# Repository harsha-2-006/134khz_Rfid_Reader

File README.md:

# 134.2 kHz RFID Reader (EM4095 + ESP32)

A low-frequency RFID reader designed and built to explore the fundamentals of LF RFID communication systems at 134.2 kHz.

This project uses the EM4095 RFID analog front-end with an ESP32 for signal processing and data handling. A custom PCB with an integrated coil antenna was designed specifically for this implementation.

---

## Overview

The system operates at 134.2 kHz and detects compatible LF RFID tags through magnetic field coupling. The EM4095 handles signal amplification and demodulation, while the ESP32 processes the received data.

The project was developed as a practical hardware learning experience covering:
- RFID communication principles
- Analog front-end interfacing
- Coil antenna design
- PCB design and testing
- Embedded firmware development

---

## Features

- 134.2 kHz low-frequency RFID operation
- Custom-designed PCB
- Integrated PCB coil antenna
- EM4095 RFID analog front-end
- ESP32-based data processing
- Compact hardware design

---

## System Architecture

1. The PCB coil antenna generates a magnetic field at 134.2 kHz.
2. When an RFID tag enters the field, the tag modulates the carrier signal.
3. The EM4095 detects and demodulates the received signal.
4. The ESP32 reads and processes the decoded data.

---

## Project Images

### PCB Layout

### 3D View

### Schematic

To refresh the images after a design change, run from `hardware/` (needs KiCad ≥ 9, `rsvg-convert` and ImageMagick):

```sh
kicad-cli pcb export svg --mode-single --fit-page-to-board --exclude-drawing-sheet --layers B.Silkscreen,B.Cu,F.Cu,F.Silkscreen,F.Fab,Edge.Cuts -o "../images/pcb.svg" "Rfid em.kicad_pcb"
rsvg-convert -w 1600 -b '#001023' "../images/pcb.svg" -o "../images/Screenshot 2026-03-31 210803.png"
kicad-cli pcb render --side top --quality high --background opaque -w 1600 --height 1000 --zoom 1.2 -o "../images/Screenshot 2026-03-31 210818.png" "Rfid em.kicad_pcb"
kicad-cli sch export svg --exclude-drawing-sheet -o ../images "Rfid em.kicad_sch"
rsvg-convert -w 4000 -b white "../images/Rfid em.svg" | magick - -trim +repage -fuzz 2% -trim +repage -bordercolor "#f5f4ef" -border 40 "../images/Screenshot 2026-03-31 210833.png"
rm "../images/pcb.svg" "../images/Rfid em.svg"
```

---

## Hardware Components

- EM4095 RFID IC
- ESP32
- Custom PCB coil antenna

---

## Repository Structure

```text
hardware/   -> PCB layout and schematic files
software/   -> ESP32 firmware
images/     -> Project images

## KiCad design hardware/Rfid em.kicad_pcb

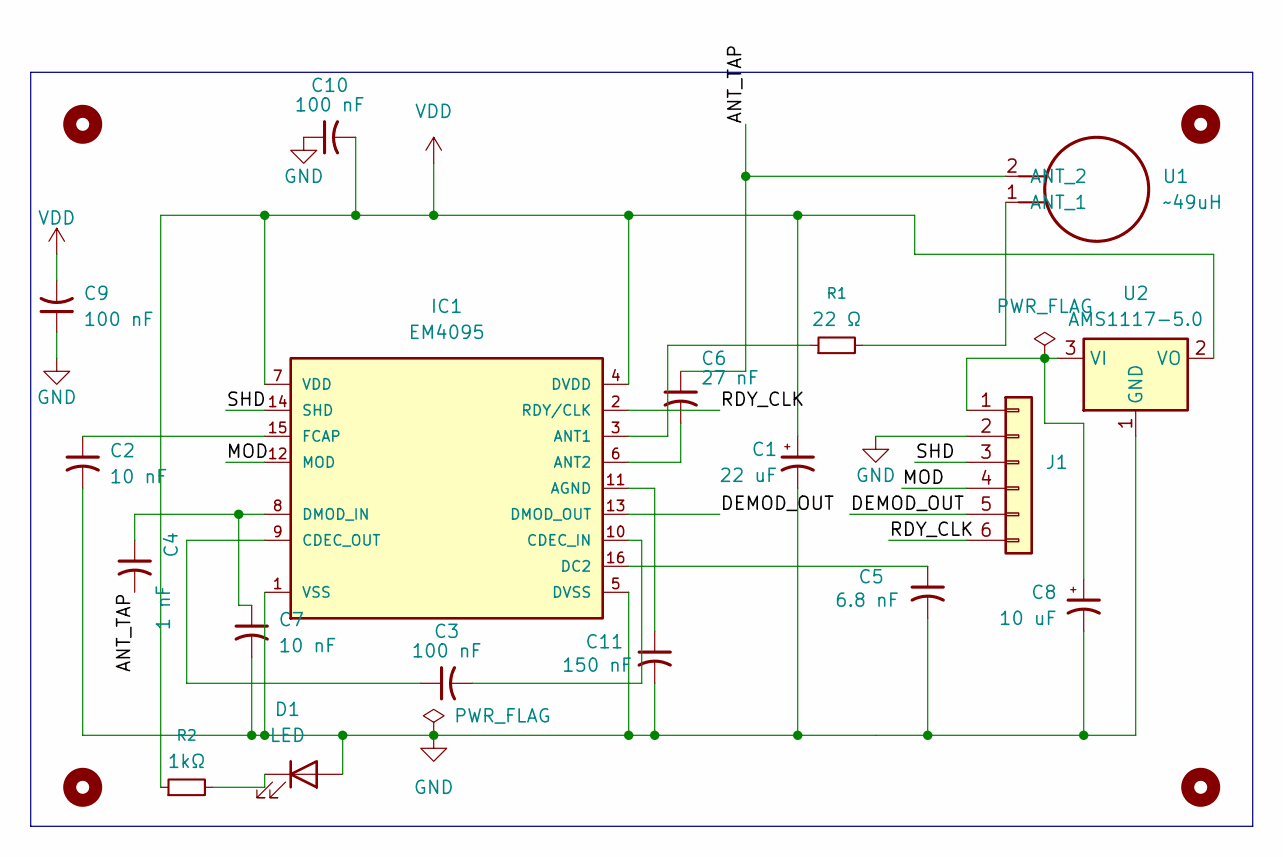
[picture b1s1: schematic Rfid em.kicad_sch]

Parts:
C1: 22 uF; CP_EIA-3528-21_Kemet-B; MPN T491B226K016AT
C2: 10 nF; C_0805_2012Metric; MPN C0805C103K5RACTU
C3, C9: 100 nF; C_0805_2012Metric; MPN GRM21BR71H104KA01L
C4: 1 nF; C_0805_2012Metric; MPN GRM2195C1H102JA01D
C5: 6.8 nF; C_0805_2012Metric; MPN C0805C682K5RACTU
C6: 27 nF; C_0805_2012Metric; MPN GRM2165C1H273JA01D
C7: 10 nF; C_0805_2012Metric; MPN GRM2195C1H103JA01D
C8: 10 uF; CP_EIA-6032-28_Kemet-C; MPN T491C106K035AT
C10: 100 nF; C_0603_1608Metric; MPN C0603C104K5RACTU
C11: 150 nF; C_0805_2012Metric; MPN C0805C154K5RACTU
D1: LED; LED_1206_3216Metric; MPN 158301250
H1, H2, H3, H4: MountingHole; MountingHole_3.5mm
IC1: EM4095; SOIC-16_3.9x9.9mm_P1.27mm; MPN EM4095HMSO16B
J1: Conn_01x06; PinHeader_1x06_P2.54mm_Vertical; MPN 61300611121
R1: 22 Ω; R_2512_6332Metric; MPN RC2512FK-0722RL
R2: 1kΩ; R_1206_3216Metric; MPN CRCW12061K00FKEA
U1: ~49uH; RFID_COIL
U2: AMS1117-5.0; SOT-223-3_TabPin2; MPN AMS1117-5.0

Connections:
/ANT_TAP: C4.2, C6.1, U1.2 (ANT_2)
/DEMOD_OUT: IC1.13 (DMOD_OUT), J1.5
/MOD: IC1.12 (MOD), J1.4
/RDY_CLK: IC1.2 (RDY/CLK), J1.6
/SHD: IC1.14 (SHD), J1.3
GND: C1.2, C2.2, C5.2, C7.2, C8.2, C9.1, C10.1, C11.2, D1.2 (A), IC1.1 (VSS), IC1.5 (DVSS), J1.2, U2.1 (GND)
unnamed: D1.1 (K), R2.2
unnamed: C11.1, IC1.11 (AGND)
unnamed: IC1.3 (ANT1), R1.1
unnamed: C6.2, IC1.6 (ANT2)
unnamed: C3.2, IC1.10 (CDEC_IN)
unnamed: C3.1, IC1.9 (CDEC_OUT)
unnamed: C5.1, IC1.16 (DC2)
unnamed: C4.1, C7.1, IC1.8 (DMOD_IN)
unnamed: C2.1, IC1.15 (FCAP)
unnamed: C8.1, J1.1, U2.3 (VI)
unnamed: R1.2, U1.1 (ANT_1)
VDD: C1.1, C9.2, C10.2, IC1.4 (DVDD), IC1.7 (VDD), R2.1, U2.2 (VO)

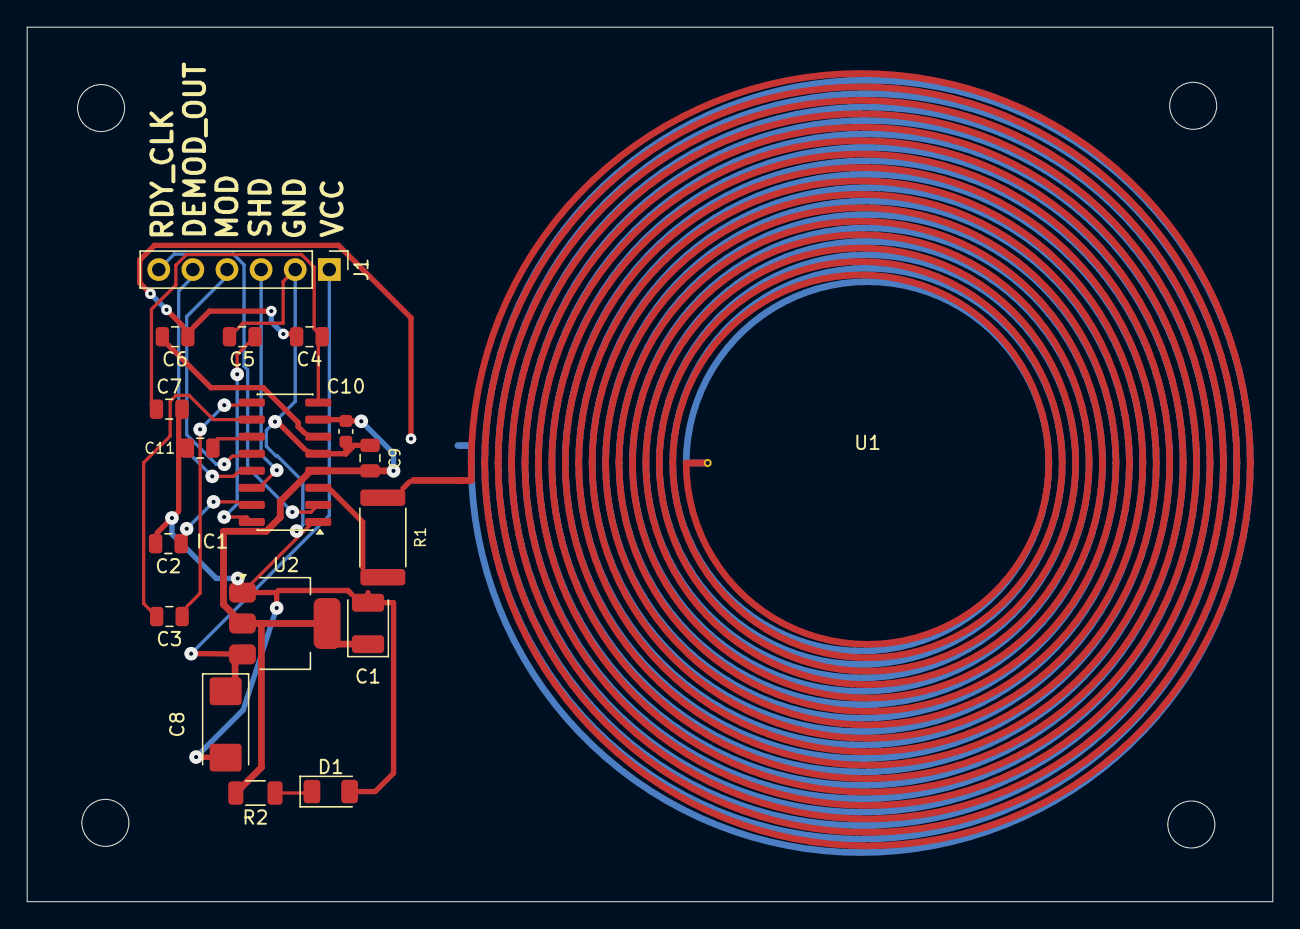
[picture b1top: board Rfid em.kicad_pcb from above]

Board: 2 copper layers, 92.7 x 65.1 mm, 22 parts (0 on the bottom side), 18 nets.

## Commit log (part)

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2026-03-31 Enhance README with project details and features
    Expanded the README with features, working details, hardware components, applications, and project status.
2026-03-31 placeholder.txt
2026-03-31 Revise README for clarity and additional information
    Updated the README to enhance project details and structure.
2026-03-31 Expand README with project details and instructions
    Added detailed project information including features, working principle, hardware used, project structure, BOM, usage instructions, improvements, applications, status, and contributions.
